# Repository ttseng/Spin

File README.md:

# Spin Turntable System

Find all the design files for building your own Spin turntable (http://spin.media.mit.edu/) here.

## Arduino

This folder contains the SoftModem library needed for the spin.ino Arduino sketch.  The spin sketch should be uploaded to the Arduino Uno running Spin.

## CAD

If you are building a turntable and have access to a laser cutter with a bed larger than 12", build the DEFAULT turntable.  If you have a smaller laser cutter that cannot cut material larger than 12", build the Modified 12-inch turntable design.  Both designs have the same exact footprint (13"), but the modified 12-inch turntable has smaller laser cut parts and has an additional set of three 3D printed feet.

Each contains three subfolders: _3D Print_, _Laser Cut_, and _Solidworks_.  Building your own Spin turntable requires laser cutting parts in 3/16" and 1/8" acrylic, which can be found in the _Laser Cut_ folder in Illustrator, Corel Draw, and DXF formats.  Additionally, you'll need to 3D print a gear (motor_gear.STL), which can be found in the _3D print_ folder.  Optionally, you can 3D print your own iOS device dock (which can be used with an iPhone 4/5/6 or iPad/iPad mini).  If you are building the modified turntable, you will also need to 3D print three feet.  

You can find all the original CAD files in the _Solidworks_ folder.

## PCB

The Eagle files and libraries for the Spin shield are located here.  You can purchase the shield directly from OSH Park: https://oshpark.com/profiles/scientiffic

## Processing

This is an optional Processing sketch for controlling the Spin turntable with your computer via a USB connection to the Uno.  You can use this to debug your turntable or to just control it without using an iOS device.

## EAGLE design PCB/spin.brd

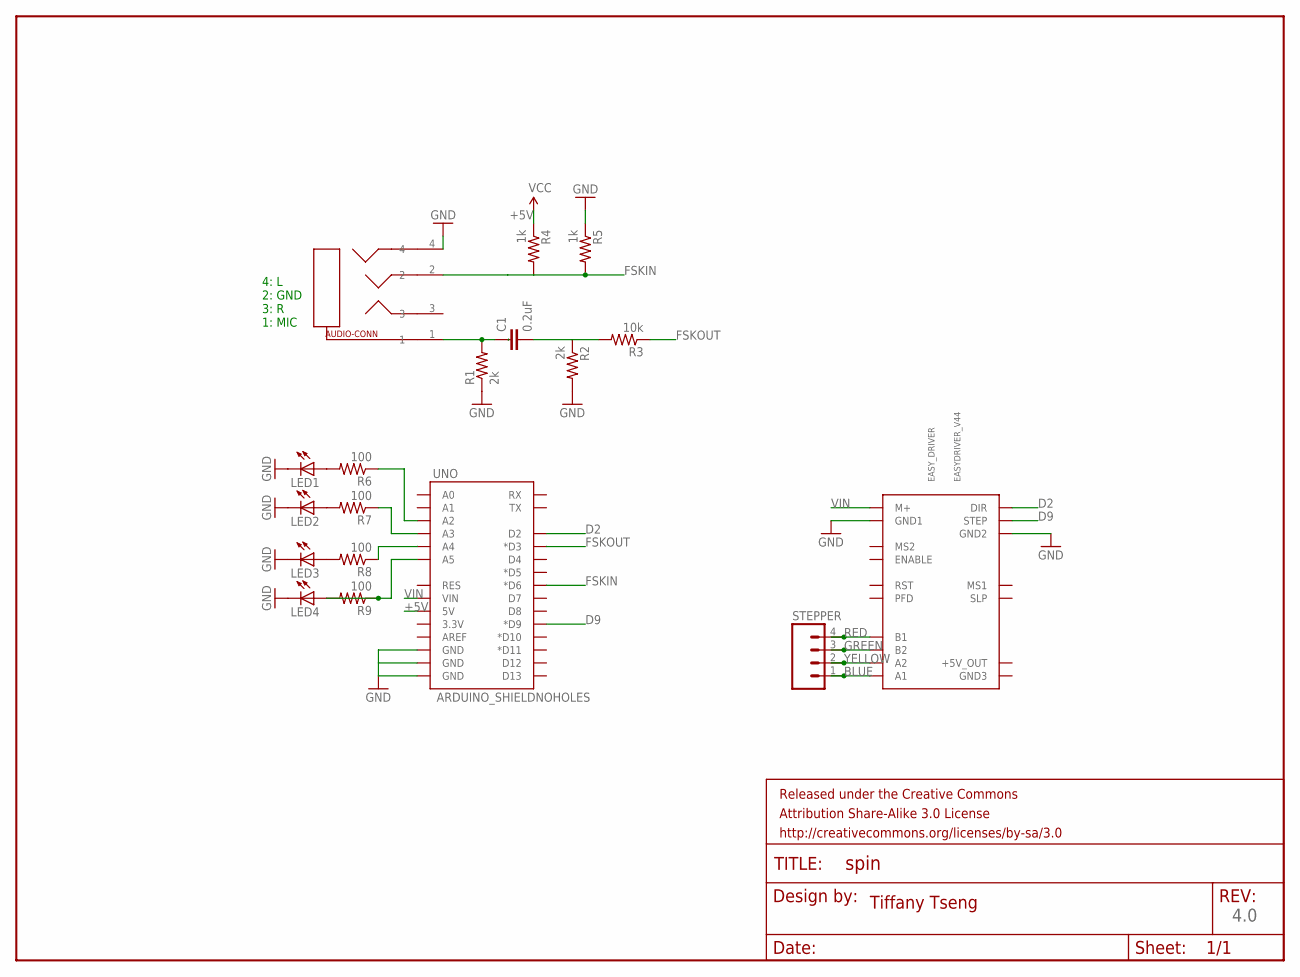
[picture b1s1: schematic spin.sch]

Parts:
C1: 0.2uF; 1206
EASY_DRIVER: EASYDRIVER_V44
FRAME1: FRAME-LETTER; CREATIVE_COMMONS
LED1, LED2, LED3, LED4: LED1206; 1206
R1, R2: 2k; R1206
R3: 10k; R1206
R4, R5: 1k; R1206
R6, R7, R8, R9: 100; R1206
STEPPER: M04PTH; 1X04
U$1: SJ-43514
UNO: ARDUINO_SHIELDNOHOLES; DUEMILANOVE_SHIELD_NOHOLES

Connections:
1: C1.1, R1.2, U$1.1
+5V: R4.1, UNO.5V
BLUE: EASY_DRIVER.A1, STEPPER.1
D2: EASY_DRIVER.DIR, UNO.D2
D9: EASY_DRIVER.STEP, UNO.D9 (*D9)
FSKIN: R4.2, R5.2, U$1.2, UNO.D6 (*D6)
FSKOUT: R3.1, UNO.D3 (*D3)
GND: EASY_DRIVER.GND1, EASY_DRIVER.GND2, LED1.2 (C), LED2.2 (C), LED3.2 (C), LED4.2 (C), R1.1, R2.2, R5.1, U$1.4, UNO.GND@0 (GND), UNO.GND@1 (GND), UNO.GND@2 (GND)
GREEN: EASY_DRIVER.B2, STEPPER.3
unnamed: C1.2, R2.1, R3.2
unnamed: R9.1, UNO.A5
unnamed: LED1.1 (A), R6.2
unnamed: LED2.1 (A), R7.2
unnamed: R8.1, UNO.A4
unnamed: LED3.1 (A), R8.2
unnamed: R7.1, UNO.A3
unnamed: LED4.1 (A), R9.2
unnamed: R6.1, UNO.A2
RED: EASY_DRIVER.B1, STEPPER.4
VIN: EASY_DRIVER.M+, UNO.VIN
YELLOW: EASY_DRIVER.A2, STEPPER.2

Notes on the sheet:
4: L 2: GND 3: R 1: MIC
4.0
Tiffany Tseng

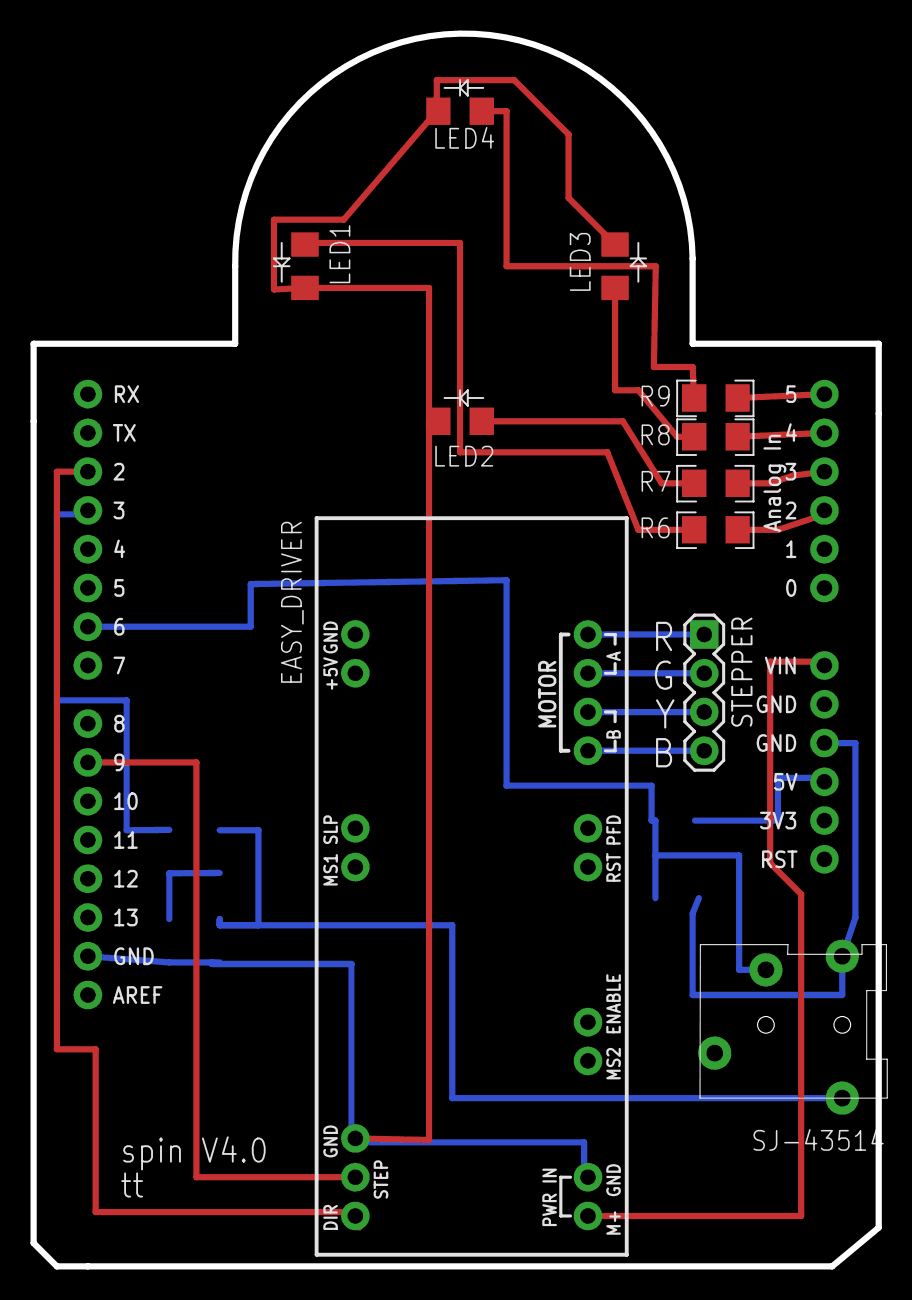
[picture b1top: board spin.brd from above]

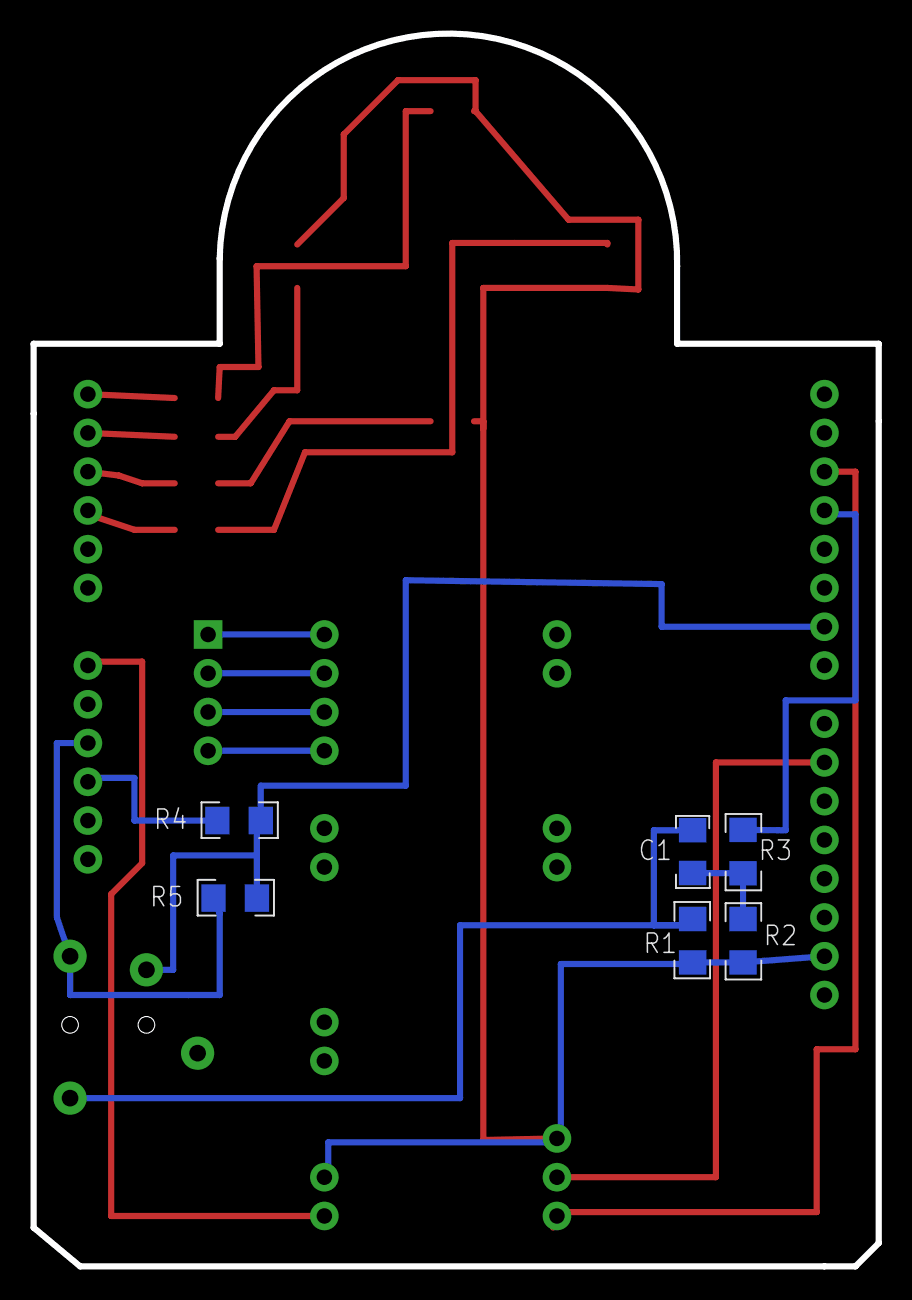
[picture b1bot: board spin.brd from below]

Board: 2 copper layers, 55.4 x 80.8 mm, 19 parts (6 on the bottom side), 21 nets.

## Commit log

2015-05-10 added design files
2015-05-11 added arduino and processing files, mat
2015-05-12 Updated iphone adapter part
2015-05-14 updated laser cut parts
2015-05-14 updated eagle files
2015-05-14 added new coreldraw file for 3/16' acrylic
2015-07-06 updated arduino code to fix communication bug
2015-07-17 updated pcb files
2015-07-19 updated spin arduino sketch
2015-07-28 updated arduino sketch for setup configuration in app
2015-09-16 added cs5 compatible dxf files and illustrator files for laser cutting
2015-10-19 added new arduino sketch for faster spins
2015-11-03 updated board silkscreen to indicate LED directions, 1206 package outlines
2016-02-12 added modified turntable design for 12-inch laser cutters
2016-04-04 added modified device dock
2016-04-05 replaced iphone dock with new ios dock
2016-07-27 updated spin arduino code for android app
2016-09-26 edited spin pcb resistor value for android communication

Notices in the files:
parts and their libraries:
SparkFun-Connectors: Licensing: CC v3.0 Share-Alike You are welcome to use this library for commercial purposes.
SparkFun-Aesthetics: Released under the Creative Commons Attribution Share-Alike 3.0 License
SparkFun-Aesthetics: http://creativecommons.org/licenses/by-sa/3.0
